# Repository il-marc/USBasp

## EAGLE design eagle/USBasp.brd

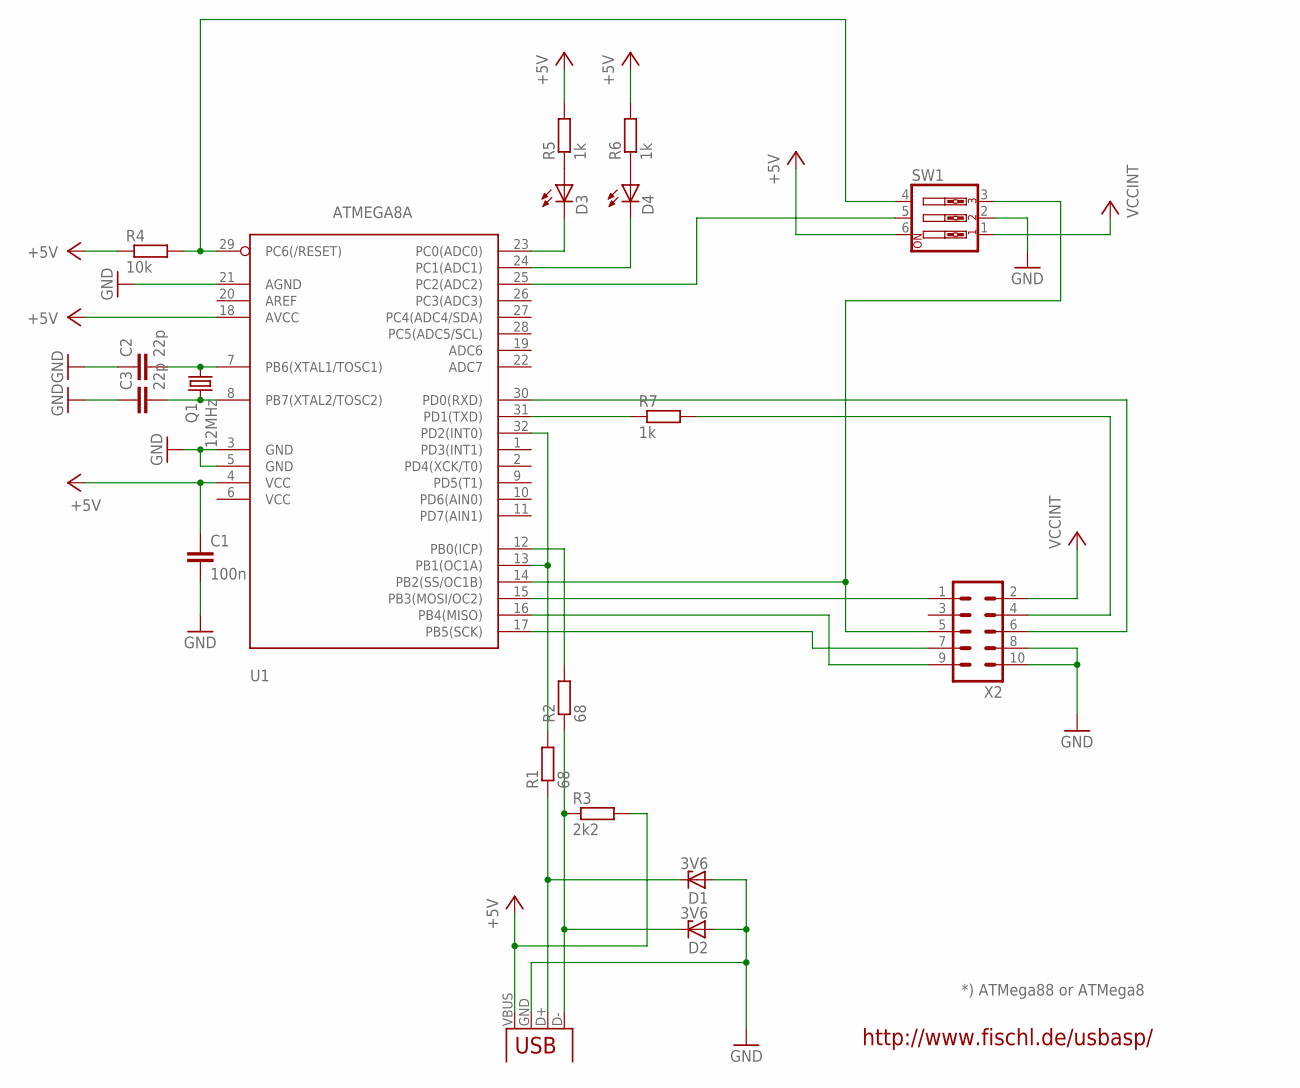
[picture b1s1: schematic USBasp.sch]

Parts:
C1: 100n; C0805
C2, C3: 22p; C0805
D1, D2: 3V6; SOD80C
D3, D4: LEDCHIPLED_0805; CHIPLED_0805
Q1: 12MHz; HC49/S
R1, R2: 68; R0805
R3: 2k2; R0805
R4: 10k; R0805
R5, R6, R7: 1k; R0805
SW1: SW_DIP-3; EDG-03
U1: ATMEGA8A; TQFP32-08
X1: USB-A-H
X2: ML10L

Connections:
+5V: C1.1, R3.2, R4.1, R5.2, R6.2, SW1.6, U1.4 (VCC), U1.18 (AVCC), X1.VBUS (GND)
GND: C1.2, C2.1, C3.1, D1.A, D2.A, SW1.2, U1.3 (GND), U1.5 (GND), U1.21 (AGND), X1.GND (VBUS), X2.8, X2.10
unnamed: R4.2, SW1.4, U1.29 (PC6(/RESET))
unnamed: SW1.3, U1.14 (PB2(SS/OC1B)), X2.5
unnamed: U1.15 (PB3(MOSI/OC2)), X2.1
unnamed: U1.17 (PB5(SCK)), X2.7
unnamed: D2.C, R2.1, R3.1, X1.D- (D+)
unnamed: U1.16 (PB4(MISO)), X2.9
unnamed: R1.2, U1.13 (PB1(OC1A)), U1.32 (PD2(INT0))
unnamed: D1.C, R1.1, X1.D+ (D-)
unnamed: R7.1, U1.31 (PD1(TXD))
unnamed: R7.2, X2.4
unnamed: U1.30 (PD0(RXD)), X2.6
unnamed: SW1.5, U1.25 (PC2(ADC2))
unnamed: D3.A, R5.1
unnamed: D3.C, U1.23 (PC0(ADC0))
unnamed: D4.C, U1.24 (PC1(ADC1))
unnamed: R2.2, U1.12 (PB0(ICP))
unnamed: D4.A, R6.1
unnamed: C2.2, Q1.2, U1.7 (PB6(XTAL1/TOSC1))
unnamed: C3.2, Q1.1, U1.8 (PB7(XTAL2/TOSC2))
VCCINT: SW1.1, X2.2

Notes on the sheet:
http://www.fischl.de/usbasp/
*) ATMega88 or ATMega8

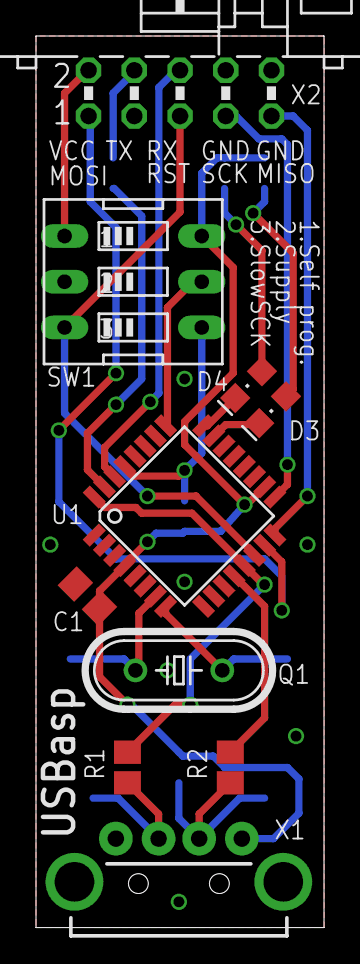
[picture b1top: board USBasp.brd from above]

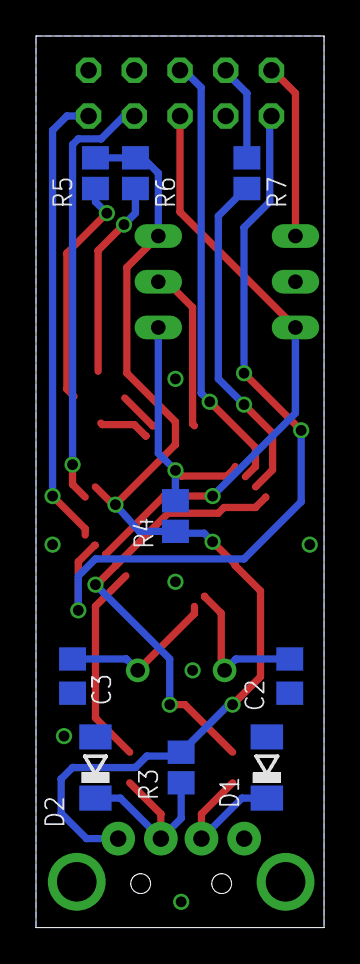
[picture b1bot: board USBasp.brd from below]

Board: 2 copper layers, 16.0 x 49.5 mm, 19 parts (9 on the bottom side), 22 nets.

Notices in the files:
parts and their libraries:
SparkFun-DigitalIC: Licensing: CC v3.0 Share-Alike You are welcome to use this library for commercial purposes.
